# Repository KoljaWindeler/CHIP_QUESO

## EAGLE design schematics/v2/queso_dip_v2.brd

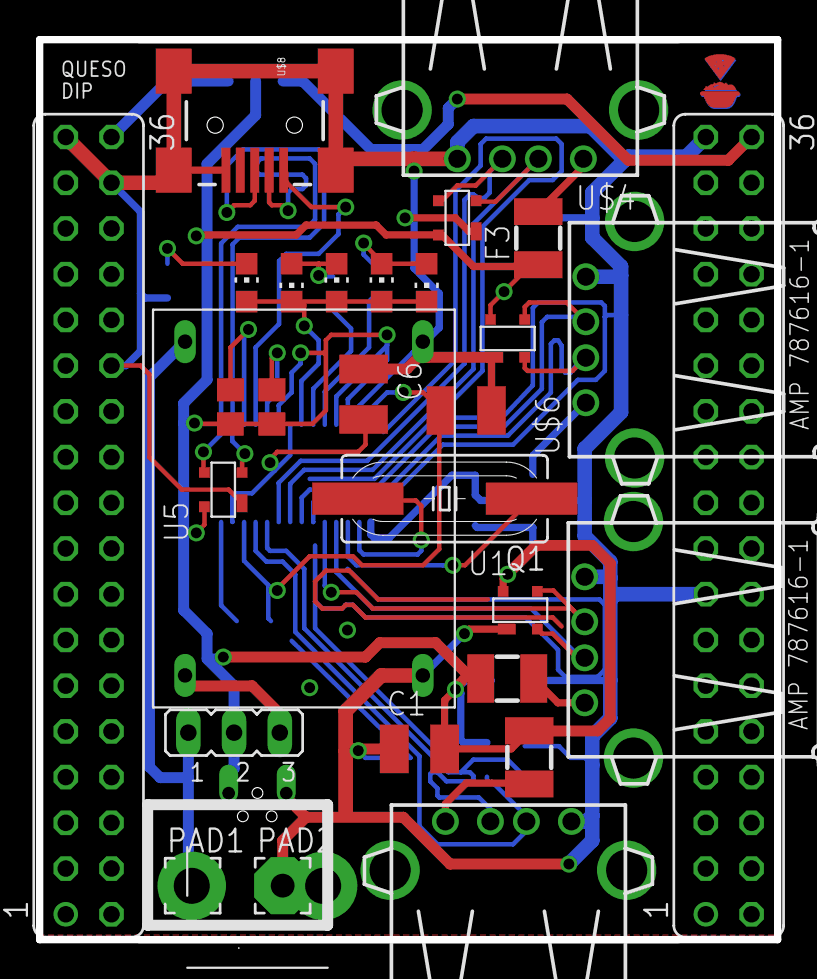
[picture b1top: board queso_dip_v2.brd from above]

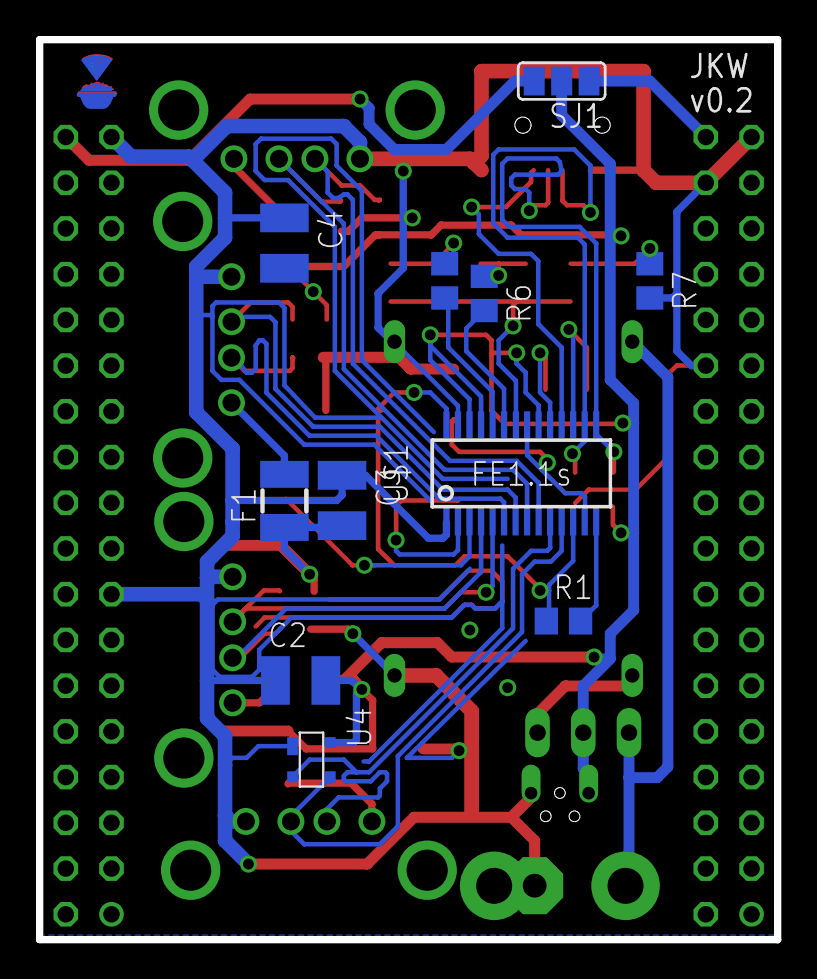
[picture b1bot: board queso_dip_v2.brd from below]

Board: 2 copper layers, 41.0 x 50.0 mm, 43 parts (12 on the bottom side), 34 nets.

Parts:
C1, C2, C3, C4, C5, C6: VJ1210V106ZXJTW1BC; C1210
F1, F2, F3, F4: PTS12066V110; 1210
JP1: JP2
LED1, LED2, LED3, LED4, LED5: 150080BS75000; CHIP-LED0805
PAD1, PAD2: WIREPAD3,17/1,3; 3,17/1,3
Q1: FOXSDLF/120-20; SM49
R1: 2.7k; R0805
R3, R4: 10k; R0805
R5, R6, R7: ERJ-6ENF3300V; R0805
SJ1: SJ_2
SV2, SV3: FE18-2
U1, U2, U3, U4, U5: PRTR5V0U2X,215; SOT-143B
U$1: FE1.1S; FE1.1S_SSOP-28
U$2, U$5: LOGO
U$3, U$4, U$6, U$7: amp 787616-1; USB_TYPE_A_FEMALE_TH
U$8: 10118194-0001LF; USB-MINIB
U$9: MP1584EN
U$10: USB-PWR; USB-MINIB-THM-MOLEX-PWRONLY

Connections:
CHIP_5V: SJ1.3, SV3.36
CHR_IN: SJ1.1, SV2.36
DM1: U4.2, U$1.10, U$3.2
DM2: U3.2, U$1.8, U$4.2
DM3: U2.2, U$1.6, U$6.2
DM4: U1.2, U$1.4, U$7.2
DMU: U5.3, U$1.15, U$8.D-
DP1: U4.3, U$1.11, U$3.3
DP2: U3.3, U$1.9, U$4.3
DP3: U2.3, U$1.7, U$6.3
DP4: U1.3, U$1.5, U$7.3
DPU: U5.2, U$1.16, U$8.D+
GND: C1.1, C2.1, C3.1, C4.1, C5.1, C6.1, PAD2.1, R7.2, SV2.26, SV2.34, SV2.35, SV3.15, SV3.35, U1.1, U2.1, U3.1, U4.1, U5.1, U$1.1, U$1.27, U$3.4, U$4.4, U$6.4, U$7.4, U$8.GND, U$8.MTN1, U$8.MTN2, U$8.MTN3, U$8.MTN4, U$9.GNDIN, U$9.GNDOUT, U$10.GND
unnamed: F2.2, U$7.1
unnamed: F1.2, U$6.1
unnamed: F3.2, U$4.1
unnamed: F4.2, U$3.1
unnamed: R5.2, U$1.24
unnamed: R6.2, U$1.23
unnamed: C6.2, U$1.13, U$1.21
unnamed: C5.2, R1.1, U$1.12, U$1.28
unnamed: R1.2, U$1.14
unnamed: R4.2, U$1.17
unnamed: R3.2, U$1.19
unnamed: Q1.2, U$1.2
unnamed: Q1.1, U$1.3
unnamed: LED5.C, R7.1
unnamed: LED3.C, LED4.A, R6.1
unnamed: LED1.A, LED2.C, R5.1
unnamed: LED1.C, LED2.A, LED3.A, LED4.C, LED5.A, U$1.22
VCC: C1.2, C2.2, C3.2, C4.2, F1.1, F2.1, F3.1, F4.1, JP1.2, R3.1, R4.1, SJ1.2, U1.4, U2.4, U3.4, U4.4, U5.4, U$1.20, U$1.25, U$1.26, U$10.VBUS
VIN: JP1.1, PAD1.1, U$9.VIN
VOUT: JP1.3, U$9.VOUT
V_UP: U$1.18, U$8.VBUS

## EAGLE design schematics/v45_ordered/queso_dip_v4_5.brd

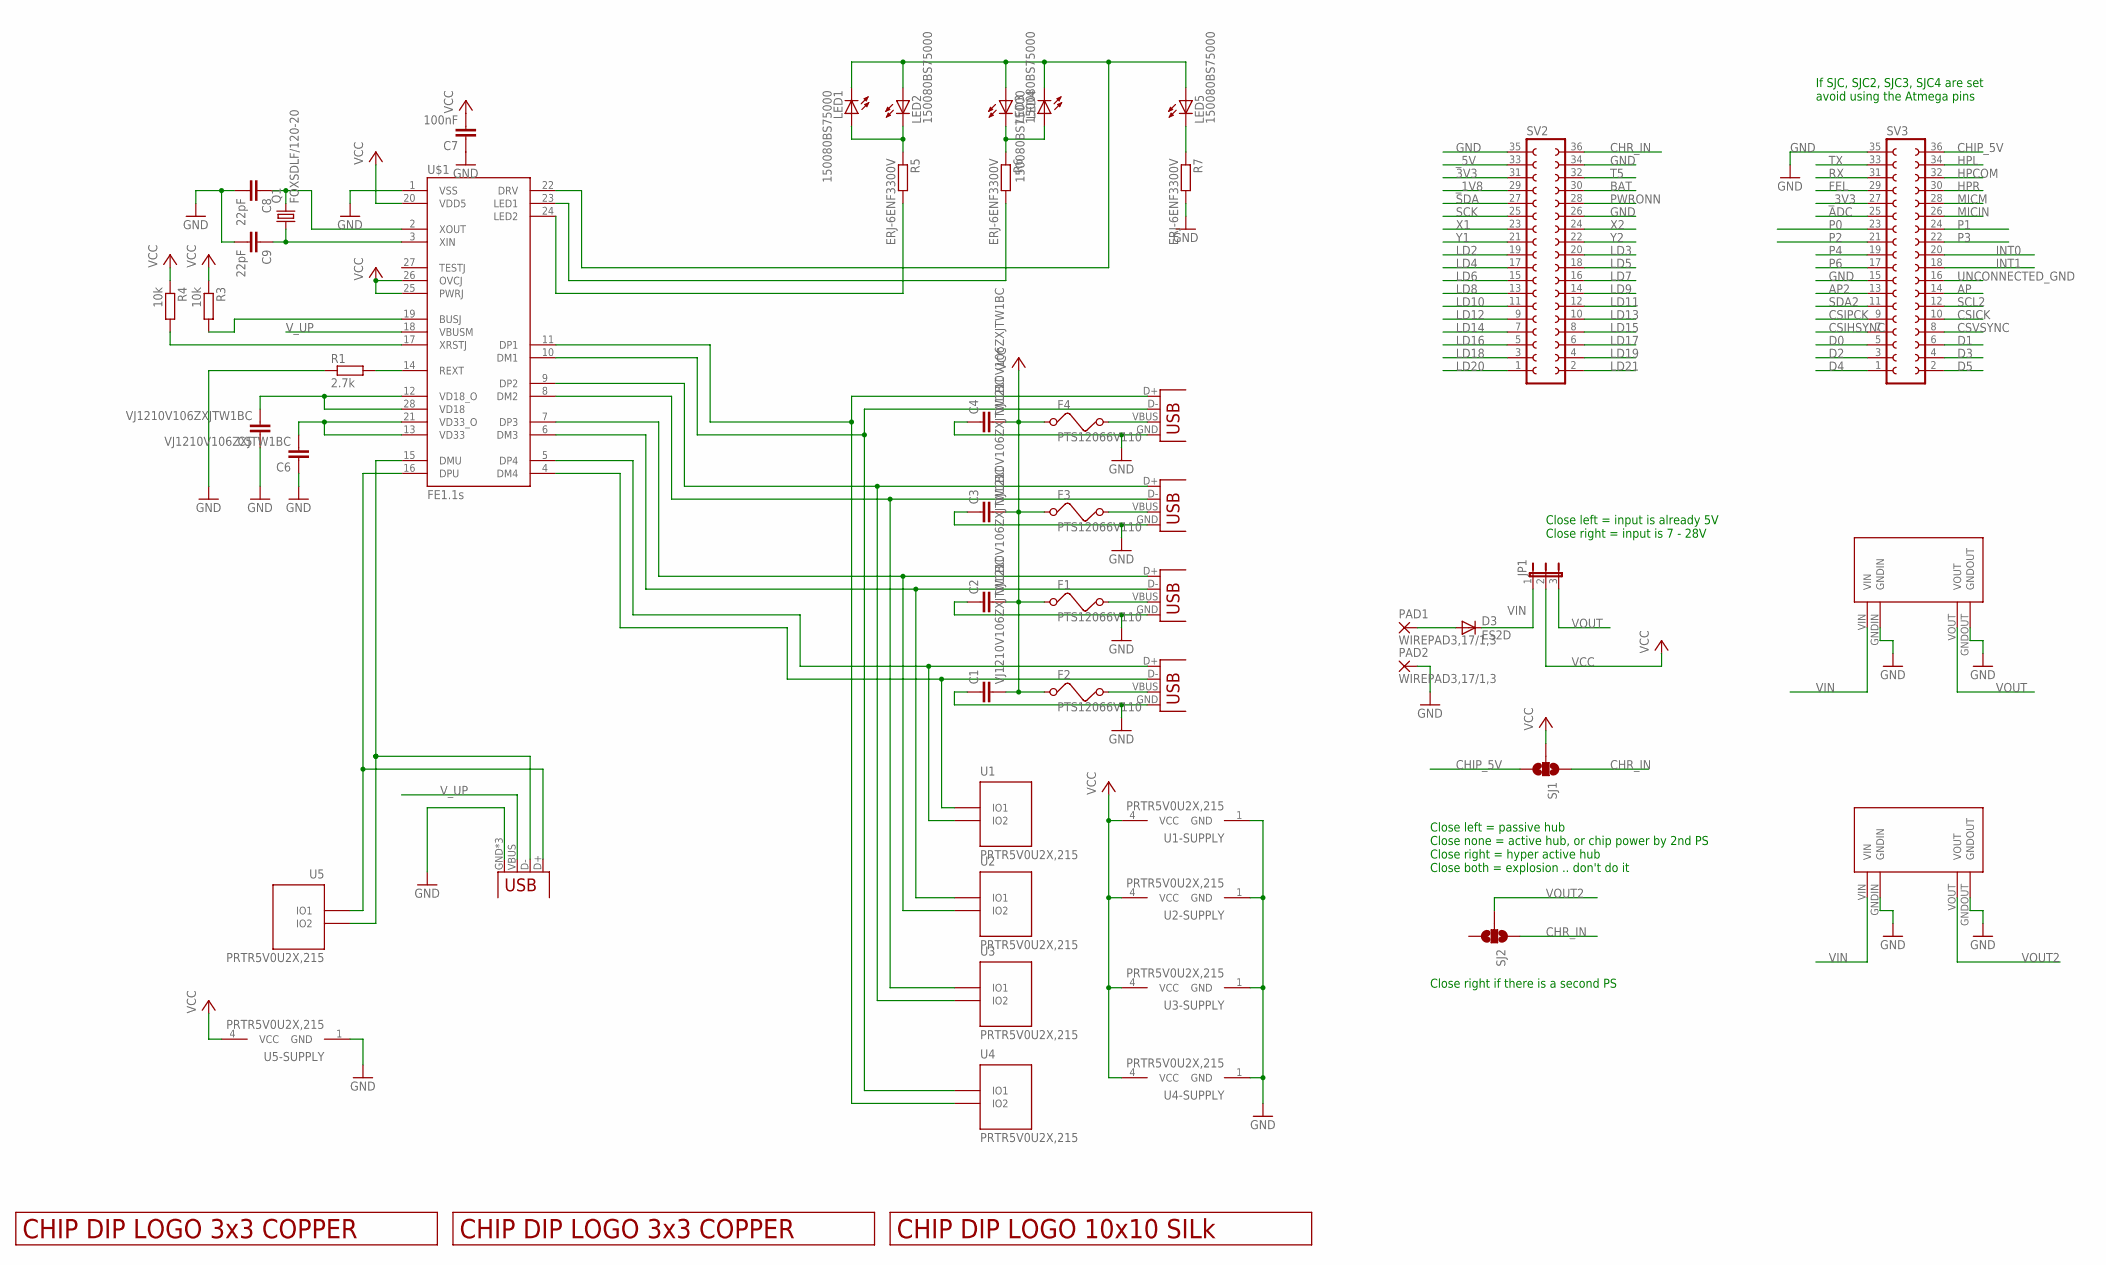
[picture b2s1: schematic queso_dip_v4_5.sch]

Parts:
C1, C2, C3, C4, C5, C6: VJ1210V106ZXJTW1BC; C1210
C7: 100nF; C0805
C8, C9: 22pF; C0805
D3: ES2D; SMB
F1, F2, F3, F4: PTS12066V110; 1210
JP1: JP2E; JP2
LED1, LED2, LED3, LED4, LED5: 150080BS75000; CHIP-LED0805
PAD1, PAD2: WIREPAD3,17/1,3; 3,17/1,3
Q1: FOXSDLF/120-20; SM49
R1: 2.7k; R0805
R3, R4: 10k; R0805
R5, R6, R7: ERJ-6ENF3300V; R0805
SJ1, SJ2: SOLDERJUMPER_2WAYT; SJ_2
SV2, SV3: FE18-2
U1, U2, U3, U4, U5: PRTR5V0U2X,215; SOT-143B
U$1: FE1.1S; FE1.1S_SSOP-28
U$2, U$4: LOGO_3X3_COPPER
U$3, U$9: MP1584EN
U$5: LOGO_10X10_SILK
USB: USBUSB-MICROB-SMT-DIP; USB-MICROB-SMT-DIP
X1, X2, X3, X4: USB-A-HU

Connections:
3V3: SV2.31
ADC: SV3.25
AP: SV3.14
AP2: SV3.13
BAT: SV2.30
CHIP_5V: SJ1.3, SV3.36
CHR_IN: SJ1.1, SJ2.1, SV2.36
CSICK: SV3.10
CSIHSYNC: SV3.7
CSIPCK: SV3.9
CSVSYNC: SV3.8
D0: SV3.5
D1: SV3.6
D2: SV3.3
D3: SV3.4
D4: SV3.1
D5: SV3.2
DM1: U4.2 (IO1), U$1.10 (DM1), X4.D-
DM2: U3.2 (IO1), U$1.8 (DM2), X3.D-
DM3: U2.2 (IO1), U$1.6 (DM3), X2.D-
DM4: U1.2 (IO1), U$1.4 (DM4), X1.D-
DMU: U5.3 (IO2), U$1.15 (DMU), USB.D-
DP1: U4.3 (IO2), U$1.11 (DP1), X4.D+
DP2: U3.3 (IO2), U$1.9 (DP2), X3.D+
DP3: U2.3 (IO2), U$1.7 (DP3), X2.D+
DP4: U1.3 (IO2), U$1.5 (DP4), X1.D+
DPU: U5.2 (IO1), U$1.16 (DPU), USB.D+
FEL: SV3.29
GND: C1.1, C2.1, C3.1, C4.1, C5.1, C6.1, C7.1, C8.2, C9.2, PAD2.1, R1.1, R7.2, SV2.26, SV2.34, SV2.35, SV3.15, SV3.35, U1.1 (GND), U2.1 (GND), U3.1 (GND), U4.1 (GND), U5.1 (GND), U$1.1 (VSS), U$3.GNDIN, U$3.GNDOUT, U$9.GNDIN, U$9.GNDOUT, USB.GND, USB.MT1 (GND), USB.MT2 (GND), X1.GND, X2.GND, X3.GND, X4.GND
HPCOM: SV3.32
HPL: SV3.34
HPR: SV3.30
INT0: SV3.20
INT1: SV3.18
LD2: SV2.19
LD3: SV2.20
LD4: SV2.17
LD5: SV2.18
LD6: SV2.15
LD7: SV2.16
LD8: SV2.13
LD9: SV2.14
LD10: SV2.11
LD11: SV2.12
LD12: SV2.9
LD13: SV2.10
LD14: SV2.7
LD15: SV2.8
LD16: SV2.5
LD17: SV2.6
LD18: SV2.3
LD19: SV2.4
LD20: SV2.1
LD21: SV2.2
MICIN: SV3.26
MICM: SV3.28
unnamed: F2.2, X1.VBUS
unnamed: D3.A, PAD1.1
unnamed: F4.2, X4.VBUS
unnamed: F1.2, X2.VBUS
unnamed: F3.2, X3.VBUS
unnamed: R5.2, U$1.24 (LED2)
unnamed: R6.2, U$1.23 (LED1)
unnamed: C6.2, U$1.13 (VD33), U$1.21 (VD33_O)
unnamed: C5.2, U$1.12 (VD18_O), U$1.28 (VD18)
unnamed: R1.2, U$1.14 (REXT)
unnamed: R4.2, U$1.17 (XRSTJ)
unnamed: R3.2, U$1.19 (BUSJ)
unnamed: C8.1, Q1.2, U$1.2 (XOUT)
unnamed: C9.1, Q1.1, U$1.3 (XIN)
unnamed: LED5.C, R7.1
unnamed: LED3.C, LED4.A, R6.1
unnamed: LED1.A, LED2.C, R5.1
unnamed: LED1.C, LED2.A, LED3.A, LED4.C, LED5.A, U$1.22 (DRV)
P0: SV3.23
P1: SV3.24
P2: SV3.21
P3: SV3.22
P4: SV3.19
P6: SV3.17
PWRONN: SV2.28
RX: SV3.31
SCK: SV2.25
SCL2: SV3.12
SDA: SV2.27
SDA2: SV3.11
T5: SV2.32
TX: SV3.33
UNCONNECTED_GND: SV3.16
VCC: C1.2, C2.2, C3.2, C4.2, C7.2, F1.1, F2.1, F3.1, F4.1, JP1.2, R3.1, R4.1, SJ1.2, U1.4 (VCC), U2.4 (VCC), U3.4 (VCC), U4.4 (VCC), U5.4 (VCC), U$1.20 (VDD5), U$1.25 (PWRJ), U$1.26 (OVCJ)
VIN: D3.C, JP1.1, U$3.VIN, U$9.VIN
VOUT: JP1.3, U$9.VOUT
VOUT2: SJ2.2, U$3.VOUT
V_UP: U$1.18 (VBUSM), USB.VBUS
X1: SV2.23
X2: SV2.24
Y1: SV2.21
Y2: SV2.22
_1V8: SV2.29
_3V3: SV3.27
_5V: SV2.33

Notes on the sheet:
If SJC, SJC2, SJC3, SJC4 are set avoid using the Atmega pins
Close left = passive hub Close none = active hub, or chip power by 2nd PS Close right = hyper active hub Close both = explosion .. don't do it
Close left = input is already 5V Close right = input is 7 - 28V
Close right if there is a second PS

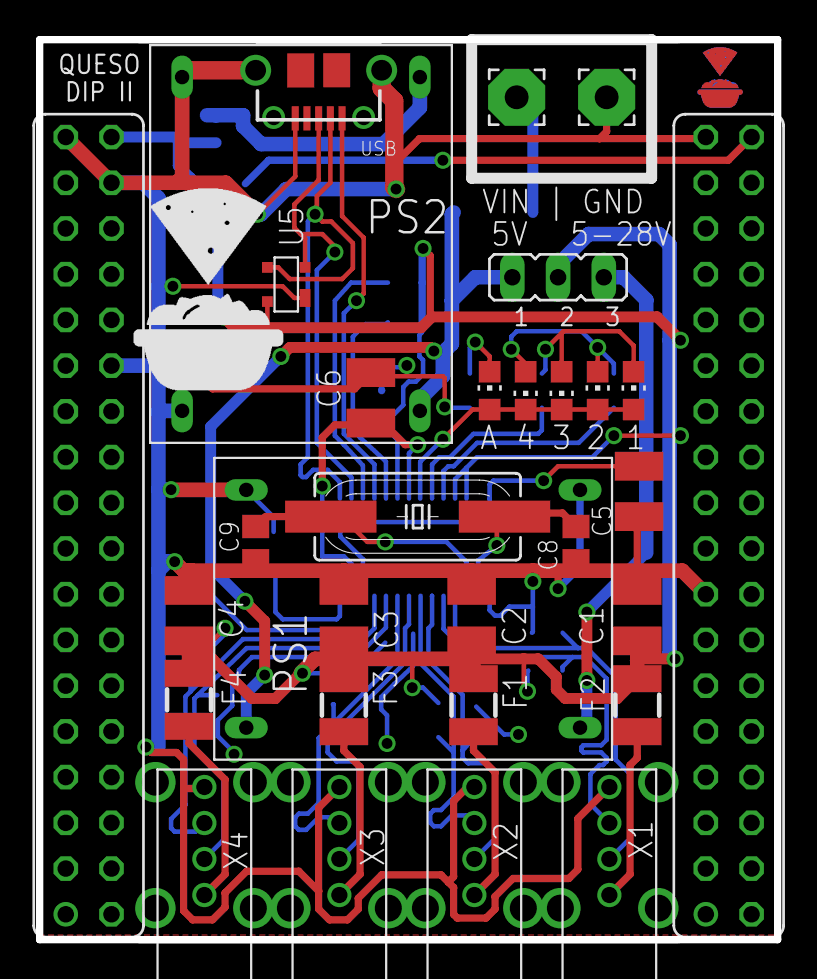
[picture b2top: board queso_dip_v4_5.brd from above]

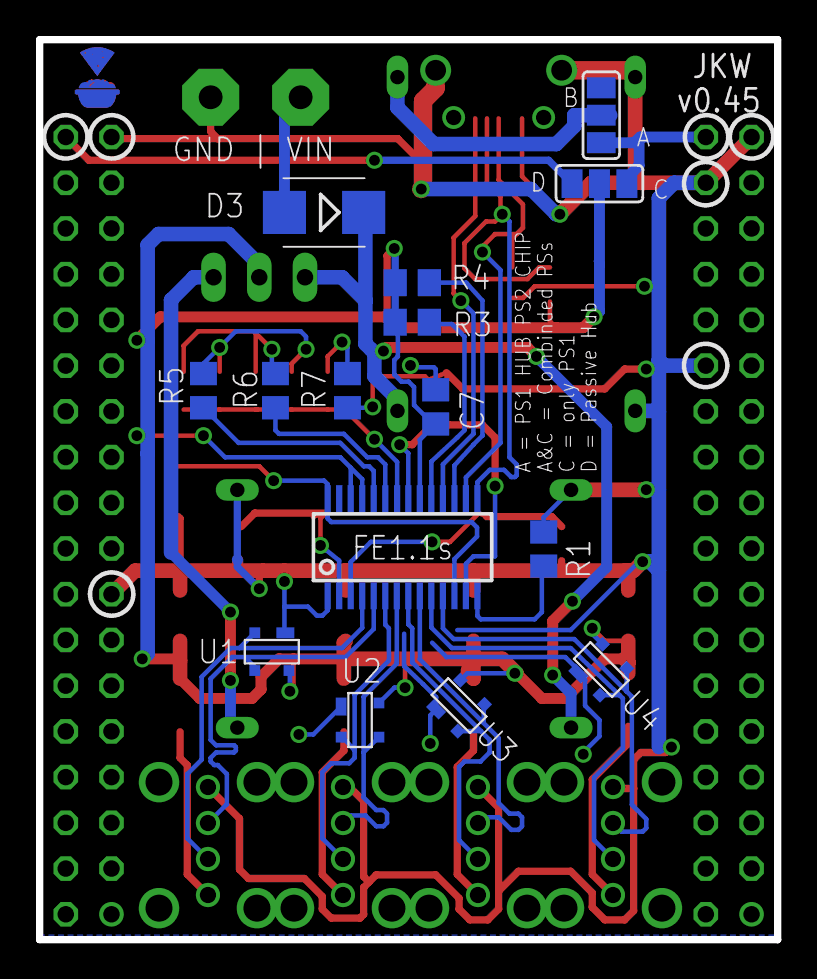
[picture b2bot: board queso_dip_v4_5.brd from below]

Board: 2 copper layers, 41.0 x 50.0 mm, 49 parts (16 on the bottom side), 36 nets.

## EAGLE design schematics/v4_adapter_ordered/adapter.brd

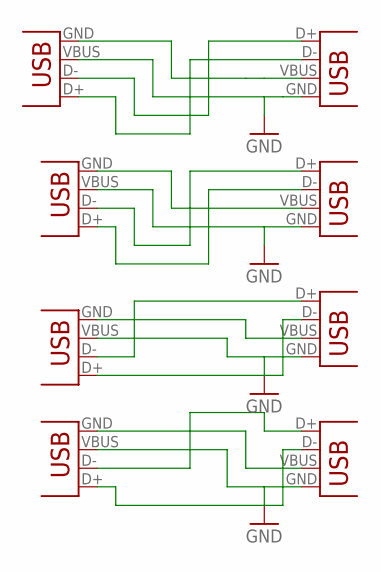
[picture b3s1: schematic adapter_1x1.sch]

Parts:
X1, X2, X3, X4, X5, X6, X7, X8: USB-A-HU

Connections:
DM1: X4.D-, X5.D+
DP1: X4.D+, X5.D-
GND: X1.GND, X2.GND, X3.GND, X4.GND, X5.VBUS, X6.VBUS, X7.VBUS, X8.VBUS
unnamed: X1.VBUS, X8.GND
unnamed: X3.D+, X6.D-
unnamed: X3.D-, X6.D+
unnamed: X2.D+, X7.D-
unnamed: X2.D-, X7.D+
unnamed: X1.D+, X8.D-
unnamed: X2.VBUS, X7.GND
unnamed: X3.VBUS, X6.GND
unnamed: X4.VBUS, X5.GND
unnamed: X1.D-, X8.D+

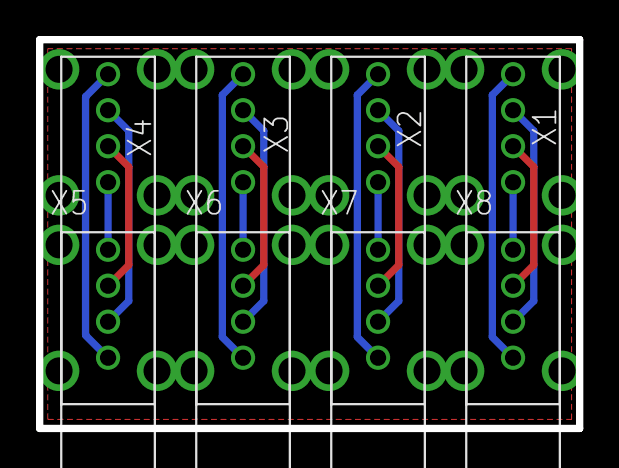
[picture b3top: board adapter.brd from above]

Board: 2 copper layers, 30.0 x 21.6 mm, 8 parts (0 on the bottom side), 13 nets.

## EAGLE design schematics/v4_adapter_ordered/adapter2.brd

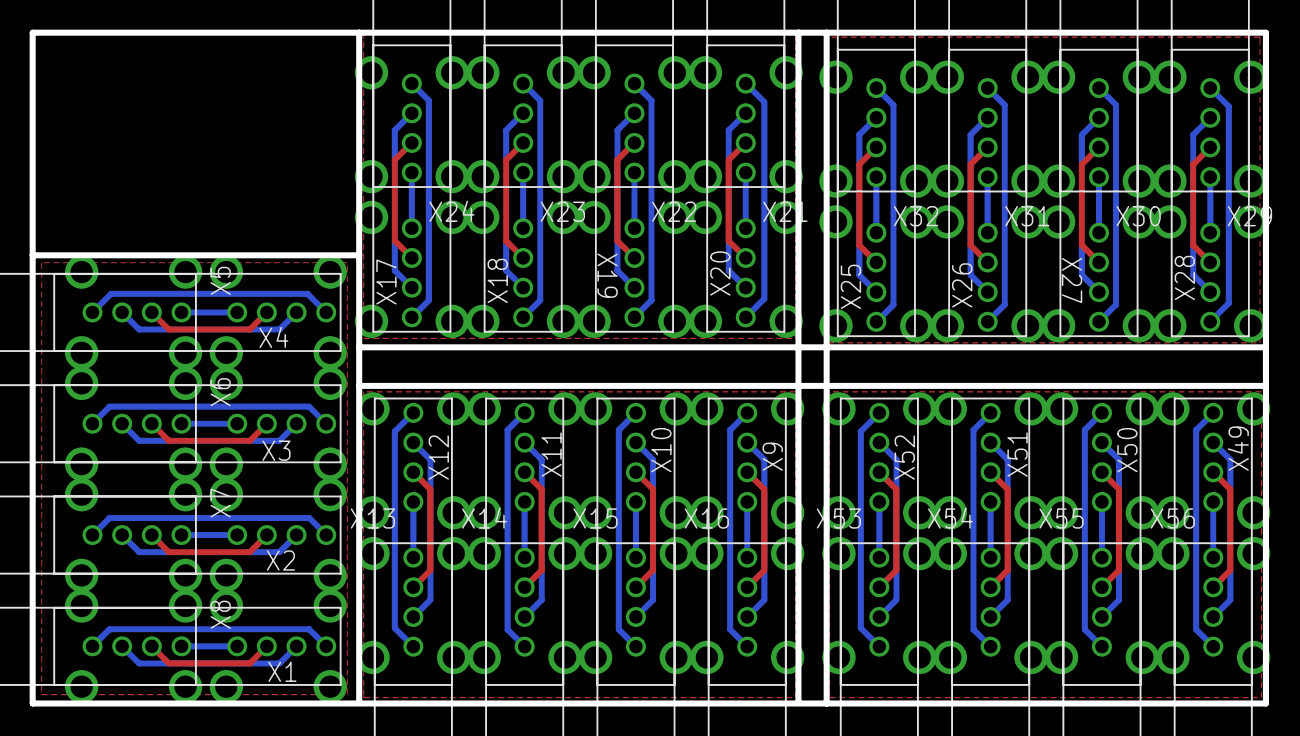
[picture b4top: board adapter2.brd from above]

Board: 2 copper layers, 83.1 x 45.2 mm, 40 parts (0 on the bottom side), 65 nets.

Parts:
X1, X2, X3, X4, X5, X6, X7, X8, X9, X10, X11, X12, X13, X14, X15, X16, X17, X18, X19, X20, X21, X22, X23, X24, X25, X26, X27, X28, X29, X30, X31, X32, X49, X50, X51, X52, X53, X54, X55, X56: USB-A-HU

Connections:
DM1: X4.D-, X5.D+
DM2: X12.D-, X13.D+
DM3: X20.D-, X21.D+
DM4: X28.D-, X29.D+
DM7: X52.D-, X53.D+
DP1: X4.D+, X5.D-
DP2: X12.D+, X13.D-
DP3: X20.D+, X21.D-
DP4: X28.D+, X29.D-
DP7: X52.D+, X53.D-
GND: X1.GND, X2.GND, X3.GND, X4.GND, X5.VBUS, X6.VBUS, X7.VBUS, X8.VBUS
GND1: X17.GND, X18.GND, X19.GND, X20.GND, X21.VBUS, X22.VBUS, X23.VBUS, X24.VBUS
GND4: X9.GND, X10.GND, X11.GND, X12.GND, X13.VBUS, X14.VBUS, X15.VBUS, X16.VBUS
GND7: X49.GND, X50.GND, X51.GND, X52.GND, X53.VBUS, X54.VBUS, X55.VBUS, X56.VBUS
GND10: X25.GND, X26.GND, X27.GND, X28.GND, X29.VBUS, X30.VBUS, X31.VBUS, X32.VBUS
unnamed: X1.VBUS, X8.GND
unnamed: X10.VBUS, X15.GND
unnamed: X3.D+, X6.D-
unnamed: X3.D-, X6.D+
unnamed: X11.VBUS, X14.GND
unnamed: X2.D+, X7.D-
unnamed: X2.D-, X7.D+
unnamed: X12.VBUS, X13.GND
unnamed: X1.D+, X8.D-
unnamed: X2.VBUS, X7.GND
unnamed: X3.VBUS, X6.GND
unnamed: X4.VBUS, X5.GND
unnamed: X1.D-, X8.D+
unnamed: X9.VBUS, X16.GND
unnamed: X11.D+, X14.D-
unnamed: X11.D-, X14.D+
unnamed: X10.D+, X15.D-
unnamed: X10.D-, X15.D+
unnamed: X9.D+, X16.D-
unnamed: X9.D-, X16.D+
unnamed: X18.VBUS, X23.GND
unnamed: X19.VBUS, X22.GND
unnamed: X20.VBUS, X21.GND
unnamed: X17.VBUS, X24.GND
unnamed: X19.D+, X22.D-
unnamed: X19.D-, X22.D+
unnamed: X18.D+, X23.D-
unnamed: X18.D-, X23.D+
unnamed: X17.D+, X24.D-
unnamed: X17.D-, X24.D+
unnamed: X26.VBUS, X31.GND
unnamed: X27.VBUS, X30.GND
unnamed: X28.VBUS, X29.GND
unnamed: X25.VBUS, X32.GND
unnamed: X27.D+, X30.D-
unnamed: X27.D-, X30.D+
unnamed: X26.D+, X31.D-
unnamed: X26.D-, X31.D+
unnamed: X25.D+, X32.D-
unnamed: X25.D-, X32.D+
unnamed: X50.VBUS, X55.GND
unnamed: X51.VBUS, X54.GND
unnamed: X52.VBUS, X53.GND
unnamed: X49.VBUS, X56.GND
unnamed: X51.D+, X54.D-
unnamed: X51.D-, X54.D+
unnamed: X50.D+, X55.D-
unnamed: X50.D-, X55.D+
unnamed: X49.D+, X56.D-
unnamed: X49.D-, X56.D+

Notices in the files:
parts and their libraries:
SparkFun-Connectors: Licensing: Creative Commons ShareAlike 4.0 International - https://creativecommons.org/licenses/by-sa/4.0
m-pad-2.1: License : GNU General Public License version 2 (see bottom)
